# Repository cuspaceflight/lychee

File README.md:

# Lychee

Lychee is a HAB (high-altitude balloon) which serves two main purposes:
- An induction project for new members looking to get hands-on building and launching a HAB.
- A test bed for prototype Martlet IV electronics.

## Motivation
After many years stuck in development hell, Project Strix (Martlet IV's avionics system) was ready for
hardware prototyping and flight testing. But flight testing avionics is difficult, especially on a budget;
so we decided to return to the society's roots and bring back our dormant HAB program.

With rough designs already complete for Martlet IV's eventual launch, we decided to port the flight
computer into a less modular form factor and consolidate modules, to create an extensible dual-board
architecture that allows us to test both fundamental system hardware and prototype future modules through
an expansion slot.

## Aims
The launch aims to test several key features and subsystems of the design ahead of construction of
final Project Strix flight hardware. In summary, these are:
- understand the embedded systems prototyping and development process for the STM32 + ChibiOS/RT stack
- perform real-time altimetry through a combination of
  - 2x redudant barometers
  - 1x 6-DoF IMU
  - 1x GPS
- relay telemetry through our custom ISM-band radio system
- verify the electrical performance of our 'blackbox' flight data recorder

## Using This Repository
This repository contains the electrical and software design files for the project. PCB designs were created
in KiCad 6, and the software was written for ChibiOS/RT. To install the dependency submodules, run
`git submodule update --init` from the root directory.

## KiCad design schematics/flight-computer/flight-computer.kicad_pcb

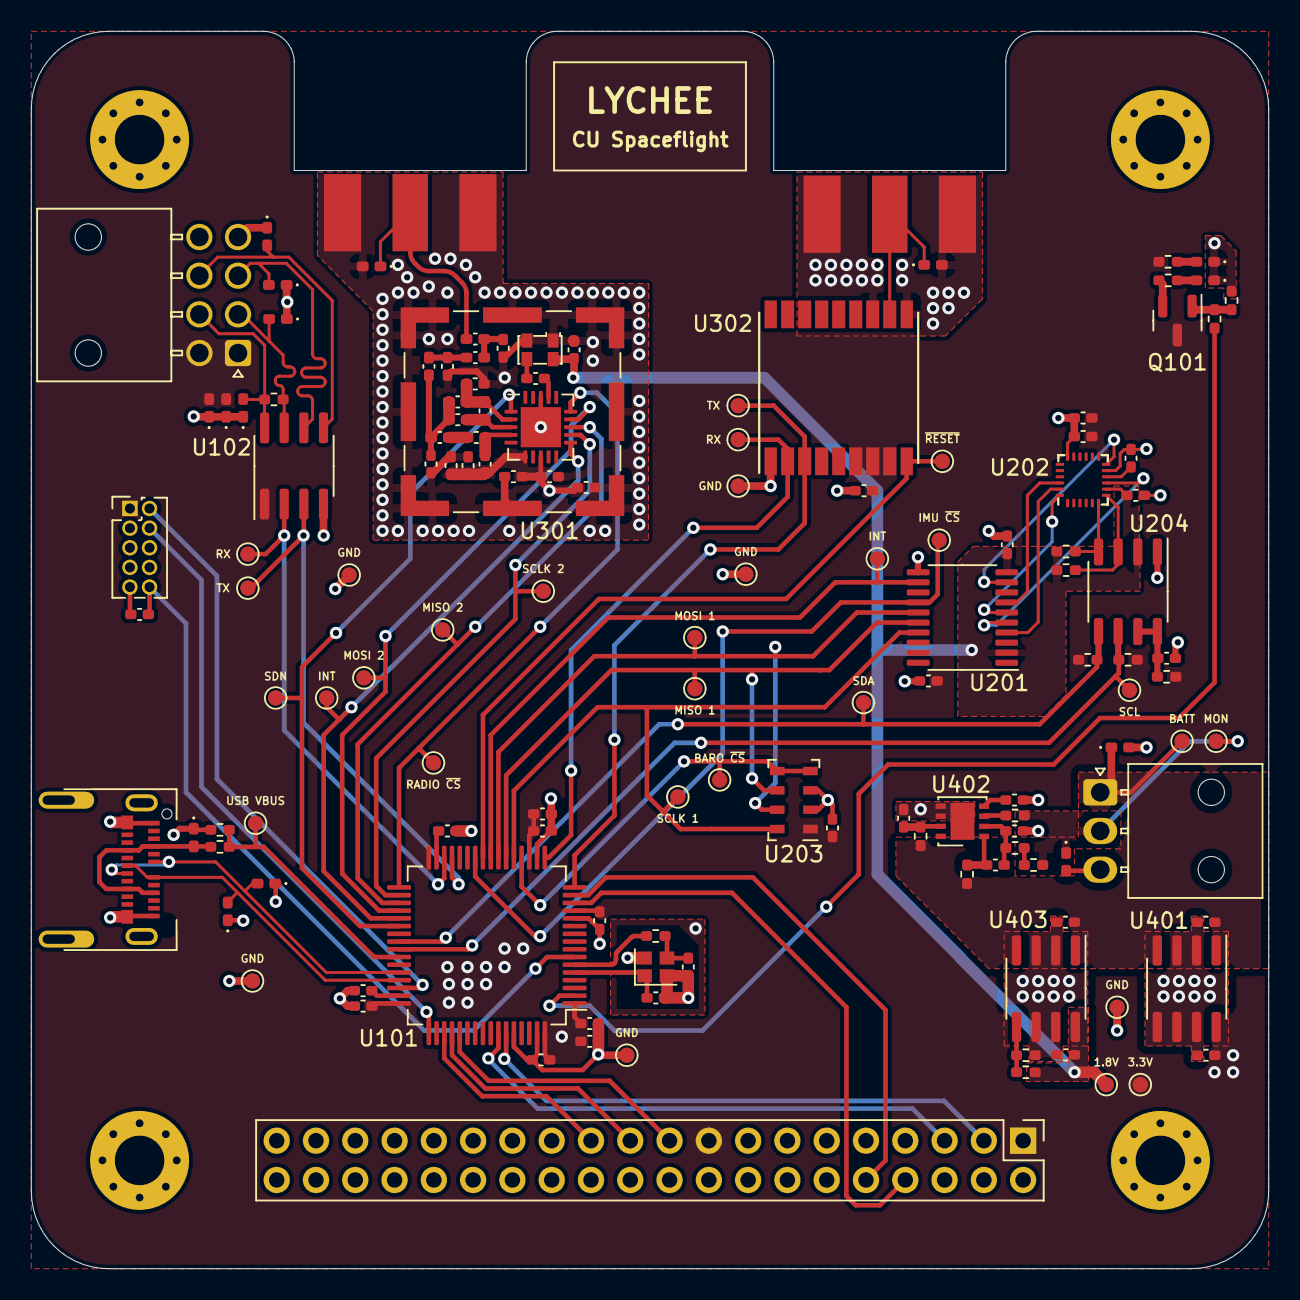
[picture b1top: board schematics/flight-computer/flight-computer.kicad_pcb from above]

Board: 4 copper layers, 80.0 x 80.0 mm, 139 parts (0 on the bottom side), 79 nets.

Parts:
1.8V, 3.3V: TestPoint
BARO ~{CS}: TestPoint
BATT: TestPoint
C101: 1µ; C_0402
C102, C103, C105, C106, C107, C110, C201, C202, C203, C205, C207, C208, C301, C311, C314, C403, C404, C405: 100n; C_0402
C104: 4µ7; C_0402
C108, C109: 2µ2; C_0402
C111, C112: 10p; C_0402
C204, C310: 2u2; C_0402
C206: 10n; C_0402
C302: 2n; C_0402
C303: 5p1; C_0402
C304: 6n8; C_0402
C305, C306: 3p3; C_0402
C307: 1p2; C_0402
C308: 3p; C_0402
C309: 1u; C_0402
C312: 220p; C_0402
C313: 100p; C_0402
C401, C402, C407, C408: 10u; C_0402
C406: 330n; C_0402
D101, D102, D103, D104, D107, D108, D109, D110, D111, D112, D113, D114, D115: D_ESD; D_0402
D105: RED; LED_0402
D106: YLW; LED_0402
GND: TestPoint
GND#2, GND#3, GND#4, GND#5, GND#6: TestPoint
H101, H102, H103, H104: MountingHole_Pad
IMU ~{CS}: TestPoint
INT: TestPoint
INT#2: TestPoint
J101: BATT; Molex_Nano-Fit_105313-1103
J102: GPS; SMA-Edge
J103: TELEM; SMA-Edge
J104: Expansion Slot; Header_RaspberryPi
J105: USB C; USB_C
J106: SWD; Header_SWD
J107: BLACKBOX; Molex_Nano-Fit_105314-1108
J301: BMI-S-201
L301: 120n; L_0402
L302: 3n3; L_0402
L303, L305: 12n; L_0402
L304, L307: 24n; L_0402
L306: 18n; L_0402
MISO 1, MISO 2: TestPoint
MON: TestPoint
MOSI 1, MOSI 2: TestPoint
Q101: BSS138
R101, R105, R401, R403, R405: 100; R_0402
R102, R103: 50; R_0402
R104: 110k; R_0402
R106, R107: 10k; R_0402
R108: 120; R_0402
R201, R407: 200k; R_0402
R202, R203, R204, R205: 4k7; R_0402
R402, R404: 160; R_0402
R406: 100k; R_0402
RADIO ~{CS}: TestPoint
RX: TestPoint
RX#2: TestPoint
SCL: TestPoint
SCLK 1, SCLK 2: TestPoint
SDA: TestPoint
SDN: TestPoint
TX: TestPoint
TX#2: TestPoint
U101: STM32F405RGT6
U102: MAX14787E
U201: NXB0108PW-Q100J
U202: ICM-20789
U203: MS5611-01BA
U204: PCA9306
U301: Si4463
U302: MAX-M8
U401, U403: MAX604
U402: BQ29200
USB VBUS: TestPoint
Y101: 26M; Xtal_SMD_2016
Y301: LFTCXO068373

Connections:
1v8: 1.8V.1, C203.2, C206.2, C301.1, C408.1, R204.2, R205.2, R406.2, U201.2 (VCC(A)), U201.10 (OE), U202.8 (VDDIO), U204.2 (VREF1), U403.8 (OUT), Y301.4 (VCC)
3v3: 3.3V.1, C101.2, C102.2, C103.2, C104.2, C105.2, C106.2, C107.2, C202.2, C204.2, C205.2, C207.2, C309.1, C310.1, C311.1, C312.1, C313.1, C314.2, C402.1, D112.2, D113.2, J104.1, J104.17, J106.1, J107.1, J107.2, L301.1, Q101.3 (D), R102.2, R201.2, R202.2, R203.2, U101.1 (VBAT), U101.13 (VDDA), U101.19 (VDD), U101.32 (VDD), U101.48 (VDD), U101.64 (VDD), U102.1 (VDD), U201.19 (VCC(B)), U202.13 (VDD), U203.1 (VDD), U301.6 (VDD), U301.8 (VDD), U302.6 (V_BCKP), U302.7 (VCC_IO), U302.8 (VCC), U401.8 (OUT)
/Altimeter/SCL_1v8: R205.1, U202.7 (PR_CL), U204.3 (SCL1)
/Altimeter/SDA_1v8: R204.1, U202.6 (PR_DA), U204.4 (SDA1)
/BARO_~CS: BARO ~{CS}.1, U101.20 (PA4), U203.4 (CSB), U203.5 (CSB)
/BATT_MON: D102.1, J101.2, MON.1, R403.1, R405.1
/BB_RX+: D114.2, J107.4, R108.1, U102.8 (A)
/BB_RX-: D111.2, J107.3, R108.2, U102.7 (B)
/BB_TX+: D115.2, J107.6, U102.5 (Y)
/BB_TX-: D110.2, J107.5, U102.6 (Z)
/GPS_~RESET: U101.25 (PC5), U302.9 (~RESET)
/I2C1_SCL: J104.5, U101.58 (PB6)
/I2C1_SDA: J104.3, U101.59 (PB7)
/I2C3_SCL: R202.1, SCL.1, U101.41 (PA8), U204.6 (SCL2)
/I2C3_SDA: R203.1, SDA.1, U101.40 (PC9), U204.5 (SDA2)
/IMU_INT: INT#2.1, U101.24 (PC4), U201.12 (B8)
/IMU_~CS: IMU ~{CS}.1, U101.26 (PB0), U201.14 (B6)
/LED: R101.1, U101.2 (PC13)
/NRST: C110.2, J106.10, U101.7 (NRST)
/RADIO_SDN: SDN.1, U101.38 (PC7), U301.1 (SDN)
/RADIO_~CS: RADIO ~{CS}.1, U101.33 (PB12), U301.15 (nSEL)
/RADIO_~INT: INT.1, U101.37 (PC6), U301.11 (nIRQ)
/Radio/ANT_GPS: D103.1, J102.1 (RF), U302.11 (RF_IN)
/Radio/ANT_TLM: D104.1, J103.1 (RF), L305.2
/Radio/RX+: C308.1, L306.2, L307.1, U301.2 (RXp)
/Radio/RX-: C307.1, L306.1, U301.3 (RXn)
/Radio/TX: C303.1, L301.2, U301.4 (TX)
/SPI1_MISO: MISO 1.1, U101.22 (PA6), U201.16 (B4), U203.6 (SDO)
/SPI1_MOSI: MOSI 1.1, U101.23 (PA7), U201.15 (B5), U203.7 (SDI/SDA)
/SPI1_SCLK: SCLK 1.1, U101.21 (PA5), U201.17 (B3), U203.8 (SCLK)
/SPI2_MISO: MISO 2.1, U101.35 (PB14), U301.13 (SDO)
/SPI2_MOSI: MOSI 2.1, U101.36 (PB15), U301.14 (SDI)
/SPI2_SCLK: SCLK 2.1, U101.34 (PB13), U301.12 (SCLK)
/SPI3_MISO: J104.21, U101.52 (PC11)
/SPI3_MOSI: J104.19, U101.53 (PC12)
/SPI3_SCLK: J104.23, U101.51 (PC10)
/SWDCLK: J106.4, U101.49 (PA14)
/SWDIO: J106.2, U101.46 (PA13)
/UART4_RX: J104.10, U101.15 (PA1)
/UART4_TX: J104.8, U101.14 (PA0)
/USART2_RX: RX#2.1, U101.17 (PA3), U302.2 (TXD)
/USART2_TX: TX.1, U101.16 (PA2), U302.3 (RXD)
/USART3_RX: RX.1, U101.30 (PB11), U102.2 (RO)
/USART3_TX: TX#2.1, U101.29 (PB10), U102.3 (DI)
/USB_FS_D+: D109.2, J105.A6 (D+), J105.B6 (D+), U101.44 (PA11)
/USB_FS_D-: D108.2, J105.A7 (D-), J105.B7 (D-), U101.45 (PA12)
/USB_FS_VBUS: R106.1, R107.2, U101.42 (PA9), USB VBUS.1
GND: C101.1, C102.1, C103.1, C104.1, C105.1, C106.1, C107.1, C108.1, C109.1, C110.1, C111.1, C112.1, C201.1, C202.1, C203.1, C204.1, C205.1, C206.1, C207.1, C208.1, C301.2, C304.2, C305.2, C306.2, C308.2, C309.2, C310.2, C311.2, C312.2, C313.2, C314.1, C401.2, C402.2, C404.2, C405.2, C406.2, C407.2, C408.2, D101.2, D102.2, D103.2, D104.2, D105.1, D106.1, D107.1, D108.1, D109.1, D110.1, D111.1, D112.1, D113.1, D114.1, D115.1, GND.1, GND#2.1, GND#3.1, GND#4.1, GND#5.1, GND#6.1, H101.1, H102.1, H103.1, H104.1, J101.3, J102.2 (GND), J103.2 (GND), J104.6, J104.9, J104.14, J104.20, J104.25, J104.30, J104.34, J104.39, J105.A1 (GND), J105.A12 (GND), J105.B1 (GND), J105.B12 (GND), J105.S1 (SHIELD), J106.3, J106.5, J106.9, J107.7, J107.8, J301.1 (Shield), R104.1, R107.1, R407.2, U101.12 (VSSA), U101.18 (VSS), U101.60 (BOOT0), U101.63 (VSS), U102.4 (GND), U201.11 (GND), U202.11 (FSYNC), U202.18 (GND), U203.2 (PS), U203.3 (GND), U204.1 (GND), U301.18 (GND), U301.21 (GND), U302.1 (GND), U302.10 (GND), U302.12 (GND), U401.2 (GND), U401.3 (GND), U401.5 (SET), U401.6 (GND), U401.7 (GND), U402.5 (GND), U402.6 (~CB_EN), U402.9 (PGND), U403.2 (GND), U403.3 (GND), U403.6 (GND), U403.7 (GND), Y101.2, Y101.4, Y301.1 (GND), Y301.2 (GND)
unnamed: C108.2, U101.31 (VCAP_1)
unnamed: C109.2, U101.47 (VCAP_2)
unnamed: C111.2, U101.5 (PH0), Y101.1
unnamed: C112.2, R105.1, Y101.3
unnamed: C201.2, U202.10 (REGOUT)
unnamed: C208.2, R201.1, U204.7 (VREF2), U204.8 (EN)
unnamed: C302.1, Y301.3 (OUT)
unnamed: C302.2, U301.17 (XIN)
unnamed: C303.2, L302.1
unnamed: C304.1, C307.2, L302.2, L303.1, L307.2
unnamed: C305.1, L303.2, L304.1
unnamed: C306.1, L304.2, L305.1
unnamed: C403.1, R402.2, U402.1 (VC2)
unnamed: C403.2, C405.1, R404.2, U402.2 (VC1)
unnamed: C404.1, R401.2, U402.7 (VDD)
unnamed: C406.1, U402.4 (CD)
unnamed: D105.2, R102.1
unnamed: D106.2, R103.1
unnamed: D107.2, J105.A4 (VBUS), J105.A9 (VBUS), J105.B4 (VBUS), J105.B9 (VBUS), R106.2
unnamed: Q101.1 (G), R101.2, R104.2
unnamed: Q101.2 (S), R103.2
unnamed: R105.2, U101.6 (PH1)
unnamed: R403.2, R404.1
unnamed: R405.2, U402.3 (VC1_CB)
unnamed: R406.1, R407.1, U403.5 (SET)
unnamed: U201.4 (A3), U202.23 (SCL/SCLK)
unnamed: U201.5 (A4), U202.9 (SDO/AD0)
unnamed: U201.6 (A5), U202.24 (SDA/SDI)
unnamed: U201.7 (A6), U202.22 (~CS)
unnamed: U201.9 (A8), U202.12 (INT)
VBATT: BATT.1, C401.1, C407.1, D101.1, J101.1, R401.1, R402.1, U401.1 (IN), U401.4 (~OFF), U403.1 (IN), U403.4 (~OFF)

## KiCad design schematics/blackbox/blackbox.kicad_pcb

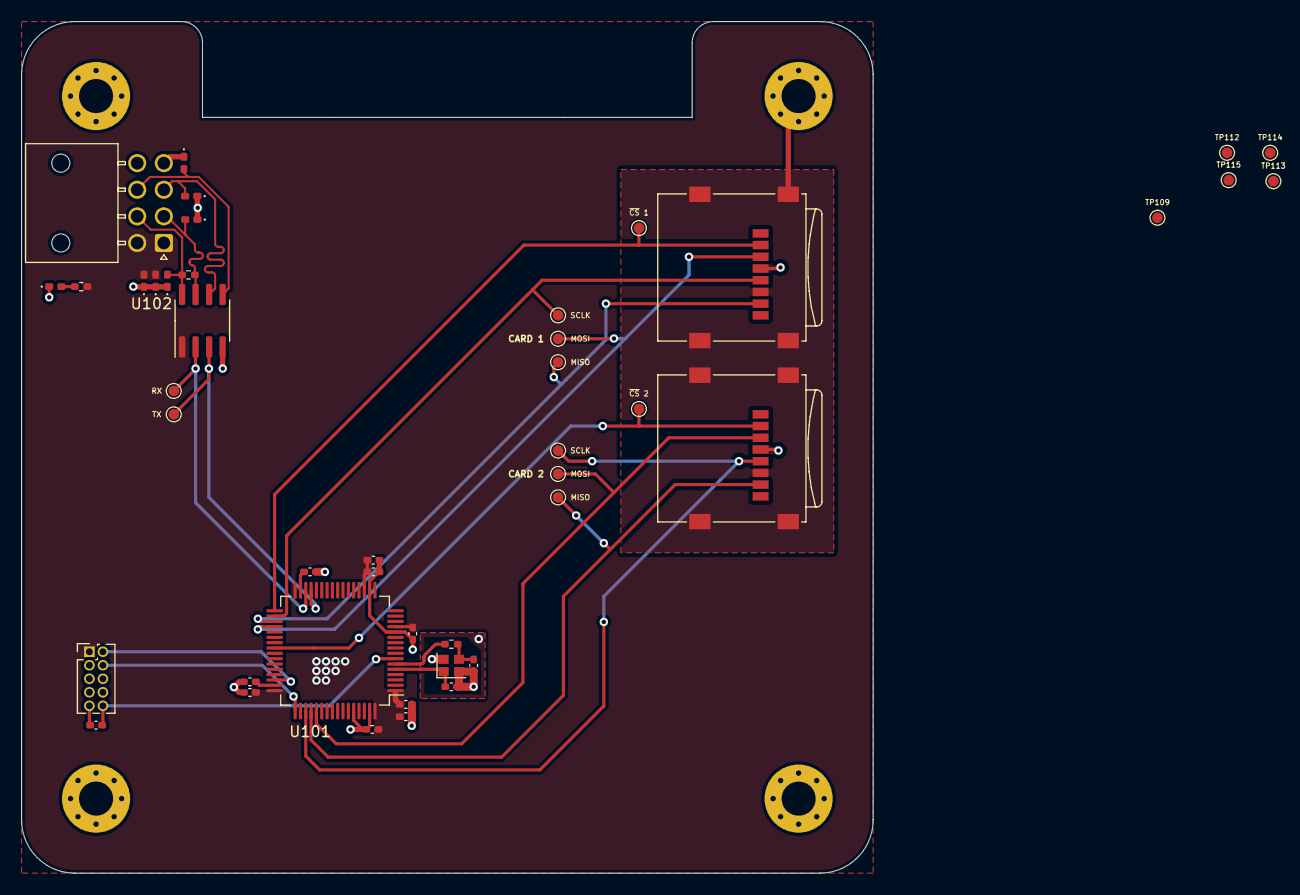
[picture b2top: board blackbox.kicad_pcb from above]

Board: 4 copper layers, 80.0 x 80.0 mm, 46 parts (0 on the bottom side), 25 nets.

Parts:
C101: 1µ; C_0402
C102, C103, C105, C106, C107, C110: 100n; C_0402
C104: 4µ7; C_0402
C108, C109: 2µ2; C_0402
C111, C112: 10p; C_0402
D101: RED; LED_0402
D102, D103, D104, D105, D106, D107: D_ESD; D_0402
H101, H102, H103, H104: MountingHole_Pad
J101, J102: Micro_SD_Card; microSD_HC_Wuerth_693072010801
J103: SWD; Header_SWD
J104: F_COMPUTER; Molex_Nano-Fit_105314-1108
MISO: TestPoint
MISO#2: TestPoint
MOSI: TestPoint
MOSI#2: TestPoint
R101: 50; R_0402
R102: 100; R_0402
R103: 120; R_0402
RX: TestPoint
SCLK: TestPoint
SCLK#2: TestPoint
TP109, TP112, TP113, TP114, TP115: TestPoint
TX: TestPoint
U101: STM32F405RGT6
U102: MAX14787E
Y101: 26M; Xtal_SMD_2016

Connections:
3v3: C101.2, C102.2, C103.2, C104.2, C105.2, C106.2, C107.2, D104.2, D105.2, J101.4 (VDD), J102.4 (VDD), J103.1, J104.1, J104.2, R101.2, TP109.1, U101.1 (VBAT), U101.13 (VDDA), U101.19 (VDD), U101.32 (VDD), U101.48 (VDD), U101.64 (VDD), U102.1 (VDD)
/BB_RX+: D106.2, J104.4, R103.1, U102.8 (A)
/BB_RX-: D103.2, J104.3, R103.2, U102.7 (B)
/BB_TX+: D107.2, J104.6, U102.5 (Y)
/BB_TX-: D102.2, J104.5, U102.6 (Z)
/NRST: C110.2, J103.10, U101.7 (NRST)
/SD1_~CS: J101.2 (DAT3/CD), U101.33 (PB12)
/SD2_~CS: J102.2 (DAT3/CD), U101.40 (PC9)
/SPI2_MISO: J101.7 (DAT0), MISO#2.1, U101.35 (PB14)
/SPI2_MOSI: J101.3 (CMD), MOSI.1, U101.36 (PB15)
/SPI2_SCLK: J101.5 (CLK), SCLK.1, U101.34 (PB13)
/SPI3_MISO: J102.7 (DAT0), MISO.1, U101.52 (PC11)
/SPI3_MOSI: J102.3 (CMD), MOSI#2.1, U101.53 (PC12)
/SPI3_SCLK: J102.5 (CLK), SCLK#2.1, U101.51 (PC10)
/SWDCLK: J103.4, U101.49 (PA14)
/SWDIO: J103.2, U101.46 (PA13)
/USART3_RX: RX.1, U101.30 (PB11), U102.2 (RO)
/USART3_TX: TX.1, U101.29 (PB10), U102.3 (DI)
GND: C101.1, C102.1, C103.1, C104.1, C105.1, C106.1, C107.1, C108.1, C109.1, C110.1, C111.1, C112.1, D101.1, D102.1, D103.1, D104.1, D105.1, D106.1, D107.1, H101.1, H102.1, H103.1, H104.1, J101.6 (VSS), J101.9 (SHIELD), J102.6 (VSS), J102.9 (SHIELD), J103.3, J103.5, J103.9, J104.7, J104.8, TP112.1, TP113.1, TP114.1, TP115.1, U101.12 (VSSA), U101.18 (VSS), U101.60 (BOOT0), U101.63 (VSS), U102.4 (GND), Y101.2, Y101.4
unnamed: C108.2, U101.31 (VCAP_1)
unnamed: C109.2, U101.47 (VCAP_2)
unnamed: C111.2, U101.5 (PH0), Y101.1
unnamed: C112.2, R102.1, Y101.3
unnamed: D101.2, R101.1
unnamed: R102.2, U101.6 (PH1)

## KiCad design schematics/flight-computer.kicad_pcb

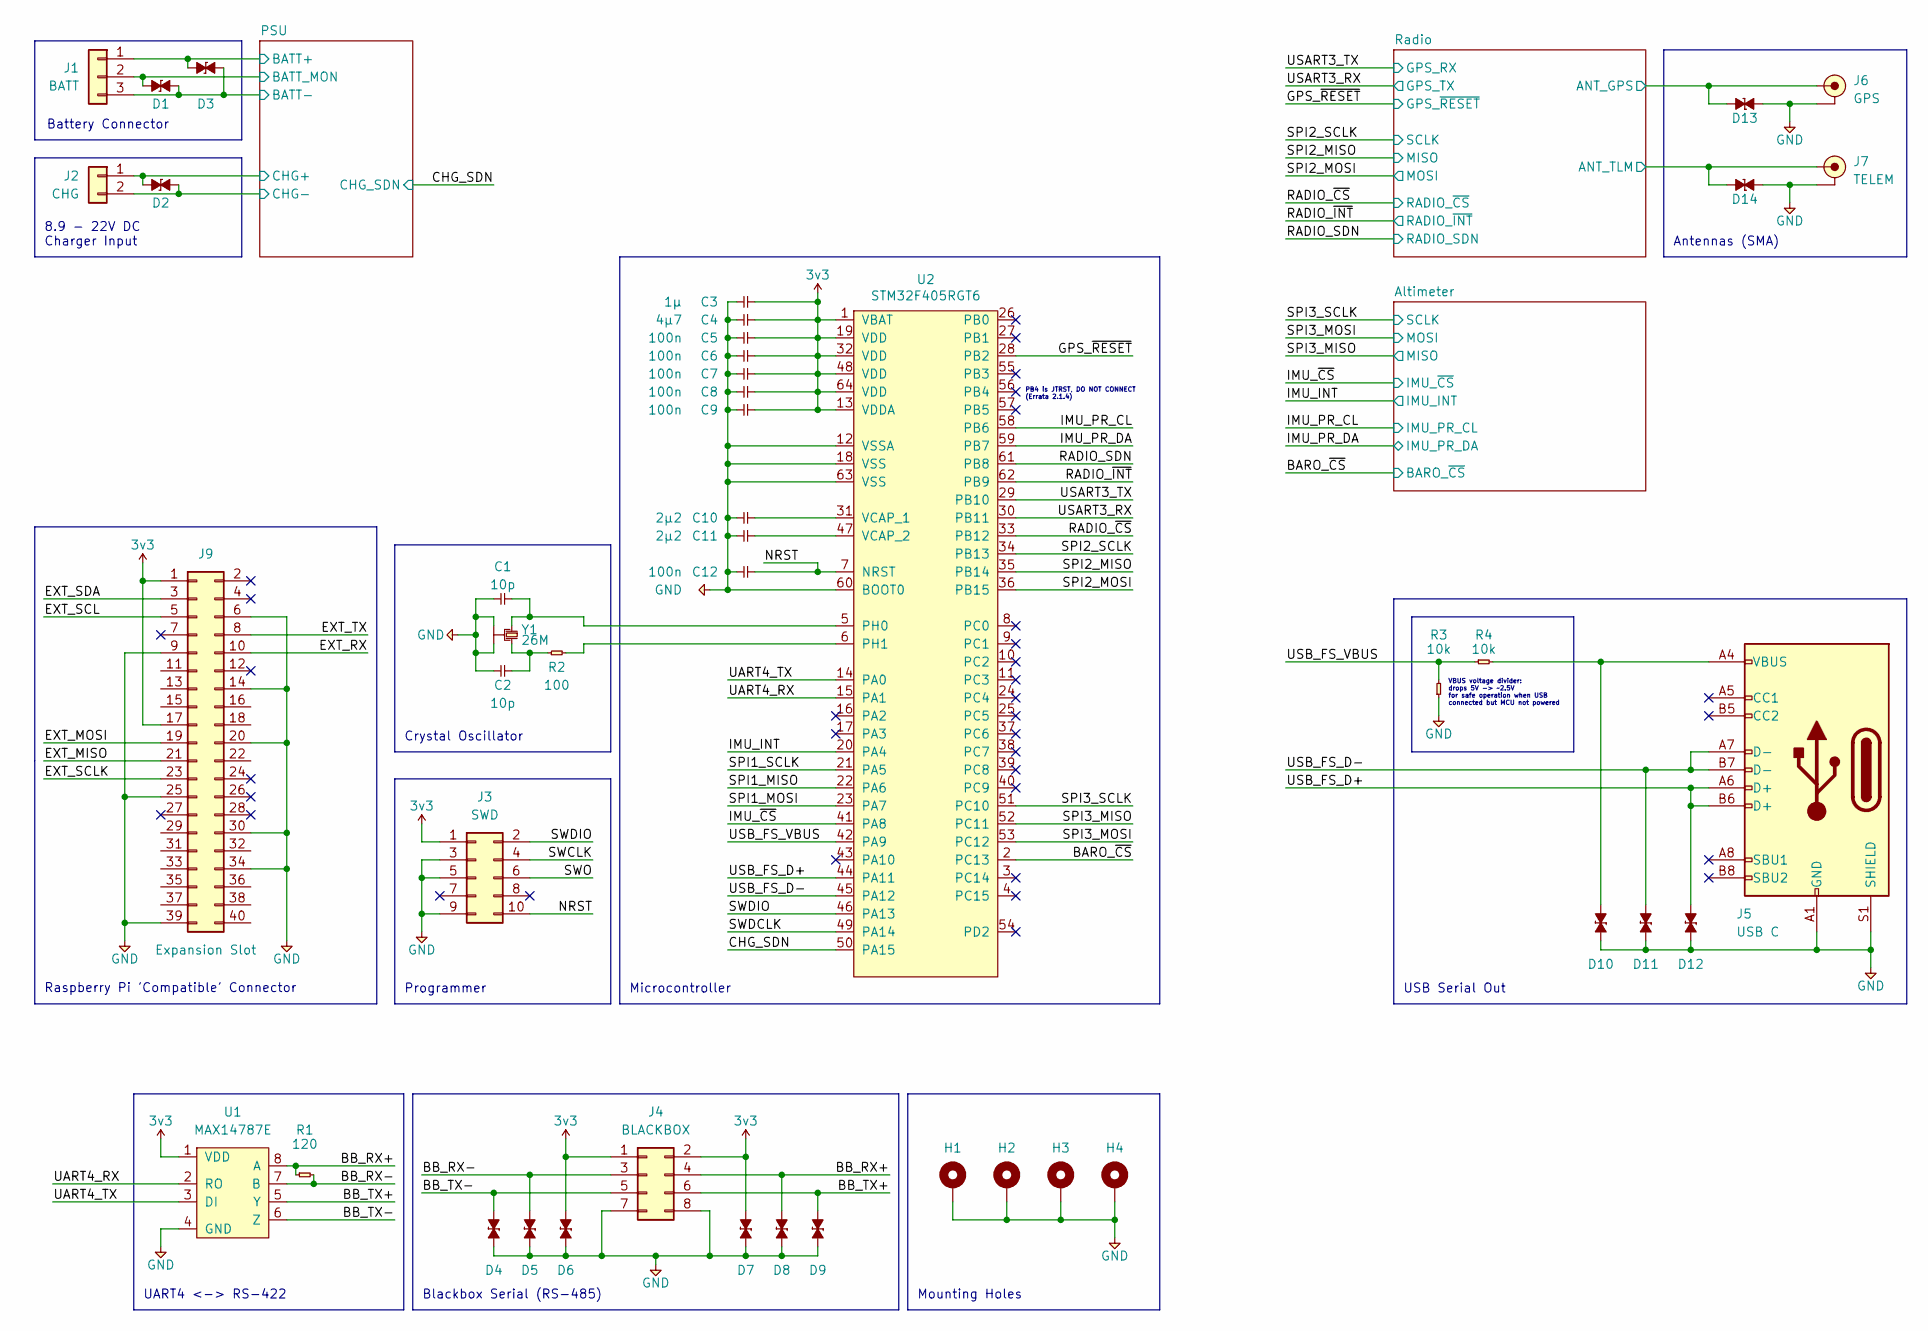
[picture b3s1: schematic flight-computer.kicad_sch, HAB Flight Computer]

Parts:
C1, C2: 10p; C_0402
C3: 1µ; C_0402; Farnell 2496814
C4: 4µ7; C_0402; Farnell 2426952
C5, C6, C7, C8, C9, C12: 100n; C_0402; Farnell 2496771
C10, C11: 2µ2; C_0402; Farnell 2362088
D1, D2, D3, D4, D5, D6, D7, D8, D9, D10, D11, D12, D13, D14: D_ESD; D_0402; Farnell 2368169
H1, H2, H3, H4: MountingHole_Pad
J1: BATT; Molex_Nano-Fit_105313-1103; Farnell 2820685
J2: CHG; Molex_Nano-Fit_105313-1102
J3: SWD; Header_SWD
J4: BLACKBOX; Molex_Nano-Fit_105314-1108
J5: USB C; USB_C; Farnell 2990003
J6: GPS; SMA-Edge; Farnell 1608592
J7: TELEM; SMA-Edge; Farnell 1608592
J9: Expansion Slot; Header_RaspberryPi
R1: 120; R_0402
R2: 100; R_0402
R3, R4: 10k; R_0402
U1: MAX14787E; Farnell 2528531
U2: STM32F405RGT6; Farnell 2064363
Y1: 26M; Xtal-20x16; Farnell 2506952

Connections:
3v3: C3.2, C4.2, C5.2, C6.2, C7.2, C8.2, C9.2, D6.2, D7.2, J3.1, J4.1, J4.2, J9.1, J9.17, U1.1 (VDD), U2.1 (VBAT), U2.13 (VDDA), U2.19 (VDD), U2.32 (VDD), U2.48 (VDD), U2.64 (VDD); also elsewhere on the board
/BARO_~CS: U2.2 (PC13); also elsewhere on the board
/BB_RX+: D8.2, J4.4, R1.1, U1.8 (A)
/BB_RX-: D5.2, J4.3, R1.2, U1.7 (B)
/BB_TX+: D9.2, J4.6, U1.5 (Y)
/BB_TX-: D4.2, J4.5, U1.6 (Z)
/CHG_SDN: U2.50 (PA15); also elsewhere on the board
/EXT_MISO: J9.21
/EXT_MOSI: J9.19
/EXT_RX: J9.10
/EXT_SCL: J9.5
/EXT_SCLK: J9.23
/EXT_SDA: J9.3
/EXT_TX: J9.8
/GPS_~RESET: U2.28 (PB2); also elsewhere on the board
/IMU_INT: U2.20 (PA4); also elsewhere on the board
/IMU_PR_CL: U2.58 (PB6); also elsewhere on the board
/IMU_PR_DA: U2.59 (PB7); also elsewhere on the board
/IMU_~CS: U2.41 (PA8); also elsewhere on the board
/NRST: C12.2, J3.10, U2.7 (NRST)
/PSU/BATT_MON: D1.1, J1.2; also elsewhere on the board
/PSU/CHG+: D2.1, J2.1; also elsewhere on the board
/RADIO_SDN: U2.61 (PB8); also elsewhere on the board
/RADIO_~CS: U2.33 (PB12); also elsewhere on the board
/RADIO_~INT: U2.62 (PB9); also elsewhere on the board
/Radio/ANT_GPS: D13.1, J6.1 (RF); also elsewhere on the board
/Radio/ANT_TLM: D14.1, J7.1 (RF); also elsewhere on the board
/SPI1_MISO: U2.22 (PA6)
/SPI1_MOSI: U2.23 (PA7)
/SPI1_SCLK: U2.21 (PA5)
/SPI2_MISO: U2.35 (PB14); also elsewhere on the board
/SPI2_MOSI: U2.36 (PB15); also elsewhere on the board
/SPI2_SCLK: U2.34 (PB13); also elsewhere on the board
/SPI3_MISO: U2.52 (PC11); also elsewhere on the board
/SPI3_MOSI: U2.53 (PC12); also elsewhere on the board
/SPI3_SCLK: U2.51 (PC10); also elsewhere on the board
/SWCLK: J3.4
/SWDCLK: U2.49 (PA14)
/SWDIO: J3.2, U2.46 (PA13)
/SWO: J3.6
/UART4_RX: U1.2 (RO), U2.15 (PA1)
/UART4_TX: U1.3 (DI), U2.14 (PA0)
/USART3_RX: U2.30 (PB11); also elsewhere on the board
/USART3_TX: U2.29 (PB10); also elsewhere on the board
/USB_FS_D+: D12.2, J5.A6 (D+), J5.B6 (D+), U2.44 (PA11)
/USB_FS_D-: D11.2, J5.A7 (D-), J5.B7 (D-), U2.45 (PA12)
/USB_FS_VBUS: R3.2, R4.1, U2.42 (PA9)
GND: C1.1, C2.1, C3.1, C4.1, C5.1, C6.1, C7.1, C8.1, C9.1, C10.1, C11.1, C12.1, D1.2, D2.2, D3.2, D4.1, D5.1, D6.1, D7.1, D8.1, D9.1, D10.1, D11.1, D12.1, D13.2, D14.2, H1.1, H2.1, H3.1, H4.1, J1.3, J2.2, J3.3, J3.5, J3.9, J4.7, J4.8, J5.A1 (GND), J5.A12 (GND), J5.B1 (GND), J5.B12 (GND), J5.S1 (SHIELD), J6.2 (GND), J7.2 (GND), J9.6, J9.9, J9.14, J9.20, J9.25, J9.30, J9.34, J9.39, R3.1, U1.4 (GND), U2.12 (VSSA), U2.18 (VSS), U2.60 (BOOT0), U2.63 (VSS), Y1.2, Y1.4; also elsewhere on the board
unnamed: C1.2, U2.5 (PH0), Y1.1
unnamed: C2.2, R2.1, Y1.3
unnamed: C10.2, U2.31 (VCAP_1)
unnamed: C11.2, U2.47 (VCAP_2)
unnamed: D10.2, J5.A4 (VBUS), J5.A9 (VBUS), J5.B4 (VBUS), J5.B9 (VBUS), R4.2
unnamed: R2.2, U2.6 (PH1)
VBATT: D3.1, J1.1; also elsewhere on the board

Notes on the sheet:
Blackbox Serial (RS-485)
USB Serial Out
PB4 is JTRST, DO NOT CONNECT (Errata 2.1.4)
Battery Connector
Mounting Holes
Crystal Oscillator
UART4 <-> RS-422
Programmer
VBUS voltage divider: drops 5V -> ~2.5V for safe operation when USB connected but MCU not powered
Microcontroller
Raspberry Pi 'Compatible' Connector
8.9 - 22V DC Charger Input
Antennas (SMA)

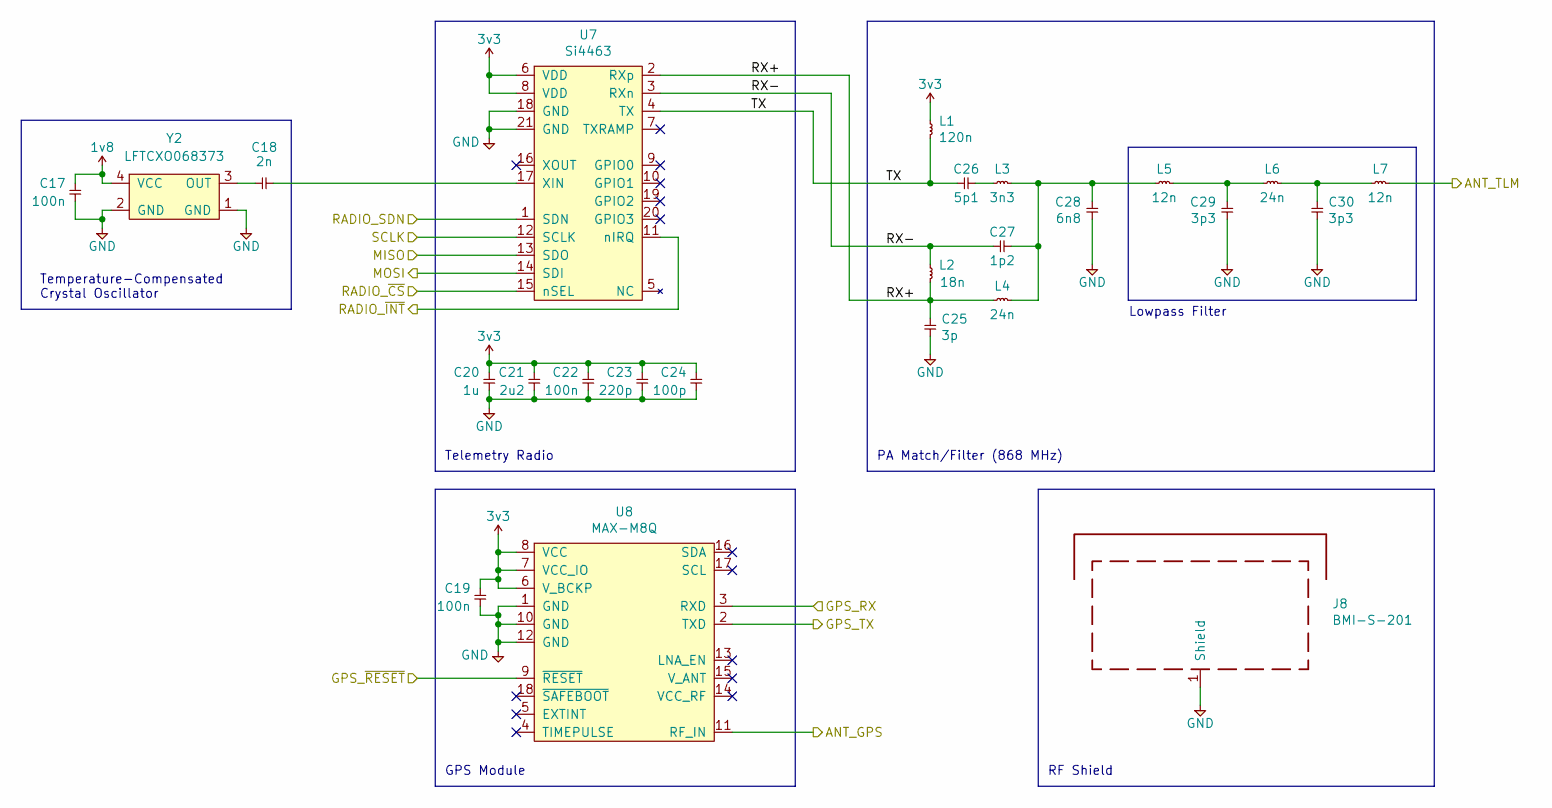
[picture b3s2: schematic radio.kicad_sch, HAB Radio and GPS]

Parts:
C17, C19, C22: 100n; C_0402
C18: 2n; C_0402
C20: 1u; C_0402
C21: 2u2; C_0402
C23: 220p; C_0402
C24: 100p; C_0402
C25: 3p; C_0402
C26: 5p1; C_0402
C27: 1p2; C_0402
C28: 6n8; C_0402
C29, C30: 3p3; C_0402
J8: BMI-S-201
L1: 120n; L_0402
L2: 18n; L_0402
L3: 3n3; L_0402
L4, L6: 24n; L_0402
L5, L7: 12n; L_0402
U7: Si4463; Farnell 2462637
U8: MAX-M8Q
Y2: LFTCXO068373; Farnell 2627327

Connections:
1v8: C17.1, Y2.4 (VCC); also elsewhere on the board
3v3: C19.2, C20.1, C21.1, C22.1, C23.1, C24.1, L1.1, U7.6 (VDD), U7.8 (VDD), U8.6 (V_BCKP), U8.7 (VCC_IO), U8.8 (VCC); also elsewhere on the board
/GPS_~RESET: U8.9 (~RESET); also elsewhere on the board
/RADIO_SDN: U7.1 (SDN); also elsewhere on the board
/RADIO_~CS: U7.15 (nSEL); also elsewhere on the board
/RADIO_~INT: U7.11 (nIRQ); also elsewhere on the board
/Radio/ANT_GPS: U8.11 (RF_IN); also elsewhere on the board
/Radio/ANT_TLM: L7.2; also elsewhere on the board
/Radio/RX+: C25.1, L2.2, L4.1, U7.2 (RXp)
/Radio/RX-: C27.1, L2.1, U7.3 (RXn)
/Radio/TX: C26.1, L1.2, U7.4 (TX)
/SPI2_MISO: U7.13 (SDO); also elsewhere on the board
/SPI2_MOSI: U7.14 (SDI); also elsewhere on the board
/SPI2_SCLK: U7.12 (SCLK); also elsewhere on the board
/USART3_RX: U8.2 (TXD); also elsewhere on the board
/USART3_TX: U8.3 (RXD); also elsewhere on the board
GND: C17.2, C19.1, C20.2, C21.2, C22.2, C23.2, C24.2, C25.2, C28.2, C29.2, C30.2, J8.1 (Shield), U7.18 (GND), U7.21 (GND), U8.1 (GND), U8.10 (GND), U8.12 (GND), Y2.1 (GND), Y2.2 (GND); also elsewhere on the board
unnamed: C18.1, Y2.3 (OUT)
unnamed: C18.2, U7.17 (XIN)
unnamed: C26.2, L3.1
unnamed: C27.2, C28.1, L3.2, L4.2, L5.1
unnamed: C29.1, L5.2, L6.1
unnamed: C30.1, L6.2, L7.1

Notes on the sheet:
PA Match/Filter (868 MHz)
Lowpass Filter
GPS Module
Telemetry Radio
Temperature-Compensated Crystal Oscillator
RF Shield

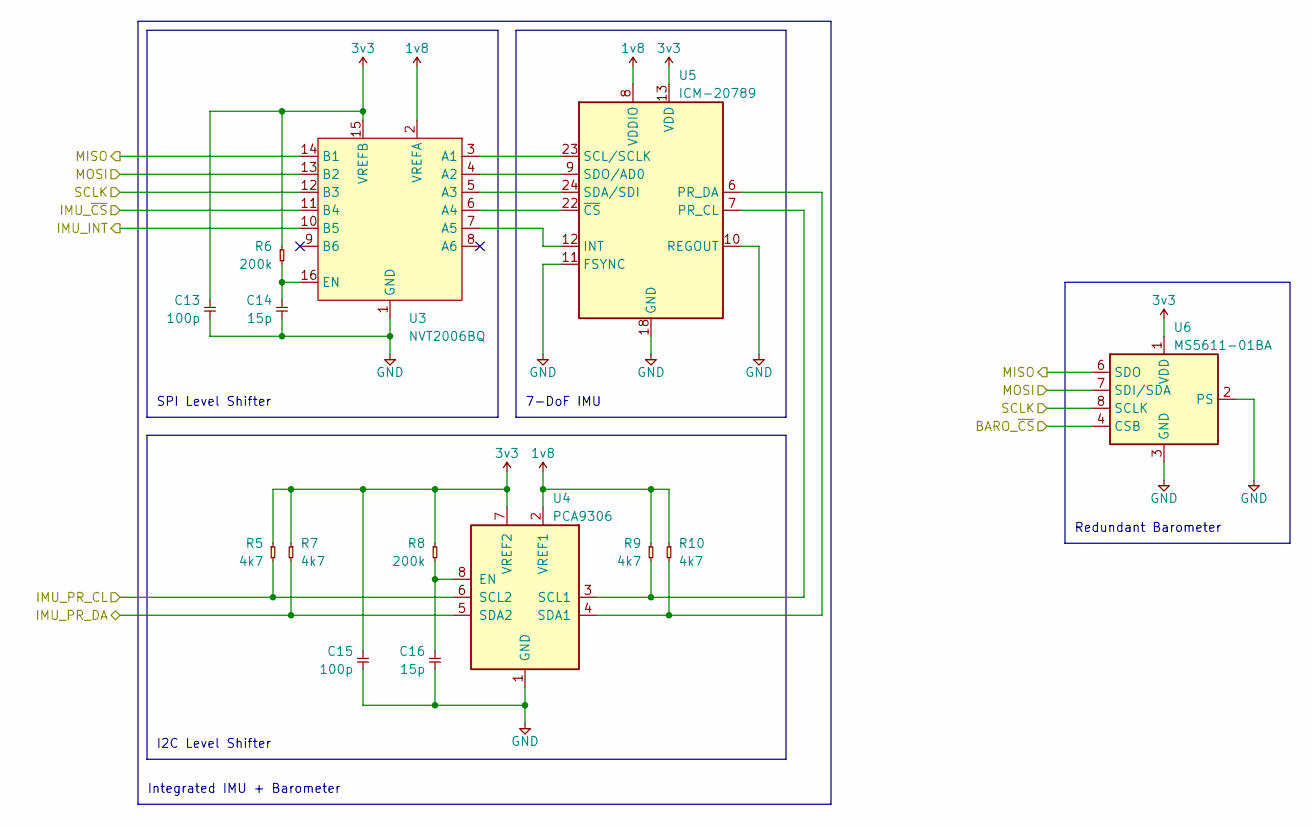
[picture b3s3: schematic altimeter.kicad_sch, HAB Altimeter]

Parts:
C13, C15: 100p; C_0402
C14, C16: 15p; C_0402
R5, R7, R9, R10: 4k7; R_0402
R6, R8: 200k; R_0402
U3: NVT2006BQ
U4: PCA9306
U5: ICM-20789
U6: MS5611-01BA

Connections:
1v8: R9.1, R10.1, U3.2 (VREFA), U4.2 (VREF1), U5.8 (VDDIO); also elsewhere on the board
3v3: C13.2, C15.2, R5.1, R6.1, R7.1, R8.1, U3.15 (VREFB), U4.7 (VREF2), U5.13 (VDD), U6.1 (VDD); also elsewhere on the board
/BARO_~CS: U6.4 (CSB), U6.5 (CSB); also elsewhere on the board
/IMU_INT: U3.10 (B5); also elsewhere on the board
/IMU_PR_CL: R5.2, U4.6 (SCL2); also elsewhere on the board
/IMU_PR_DA: R7.2, U4.5 (SDA2); also elsewhere on the board
/IMU_~CS: U3.11 (B4); also elsewhere on the board
/SPI3_MISO: U3.14 (B1), U6.6 (SDO); also elsewhere on the board
/SPI3_MOSI: U3.13 (B2), U6.7 (SDI/SDA); also elsewhere on the board
/SPI3_SCLK: U3.12 (B3), U6.8 (SCLK); also elsewhere on the board
GND: C13.1, C14.1, C15.1, C16.1, U3.1 (GND), U4.1 (GND), U5.10 (REGOUT), U5.11 (FSYNC), U5.18 (GND), U5.20 (NC), U6.2 (PS), U6.3 (GND); also elsewhere on the board
unnamed: C14.2, R6.2, U3.16 (EN)
unnamed: C16.2, R8.2, U4.8 (EN)
unnamed: R9.2, U4.3 (SCL1), U5.7 (PR_CL)
unnamed: R10.2, U4.4 (SDA1), U5.6 (PR_DA)
unnamed: U3.3 (A1), U5.23 (SCL/SCLK)
unnamed: U3.4 (A2), U5.9 (SDO/AD0)
unnamed: U3.5 (A3), U5.24 (SDA/SDI)
unnamed: U3.6 (A4), U5.22 (~CS)
unnamed: U3.7 (A5), U5.12 (INT)

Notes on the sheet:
SPI Level Shifter
Integrated IMU + Barometer
Redundant Barometer
I2C Level Shifter
7-DoF IMU

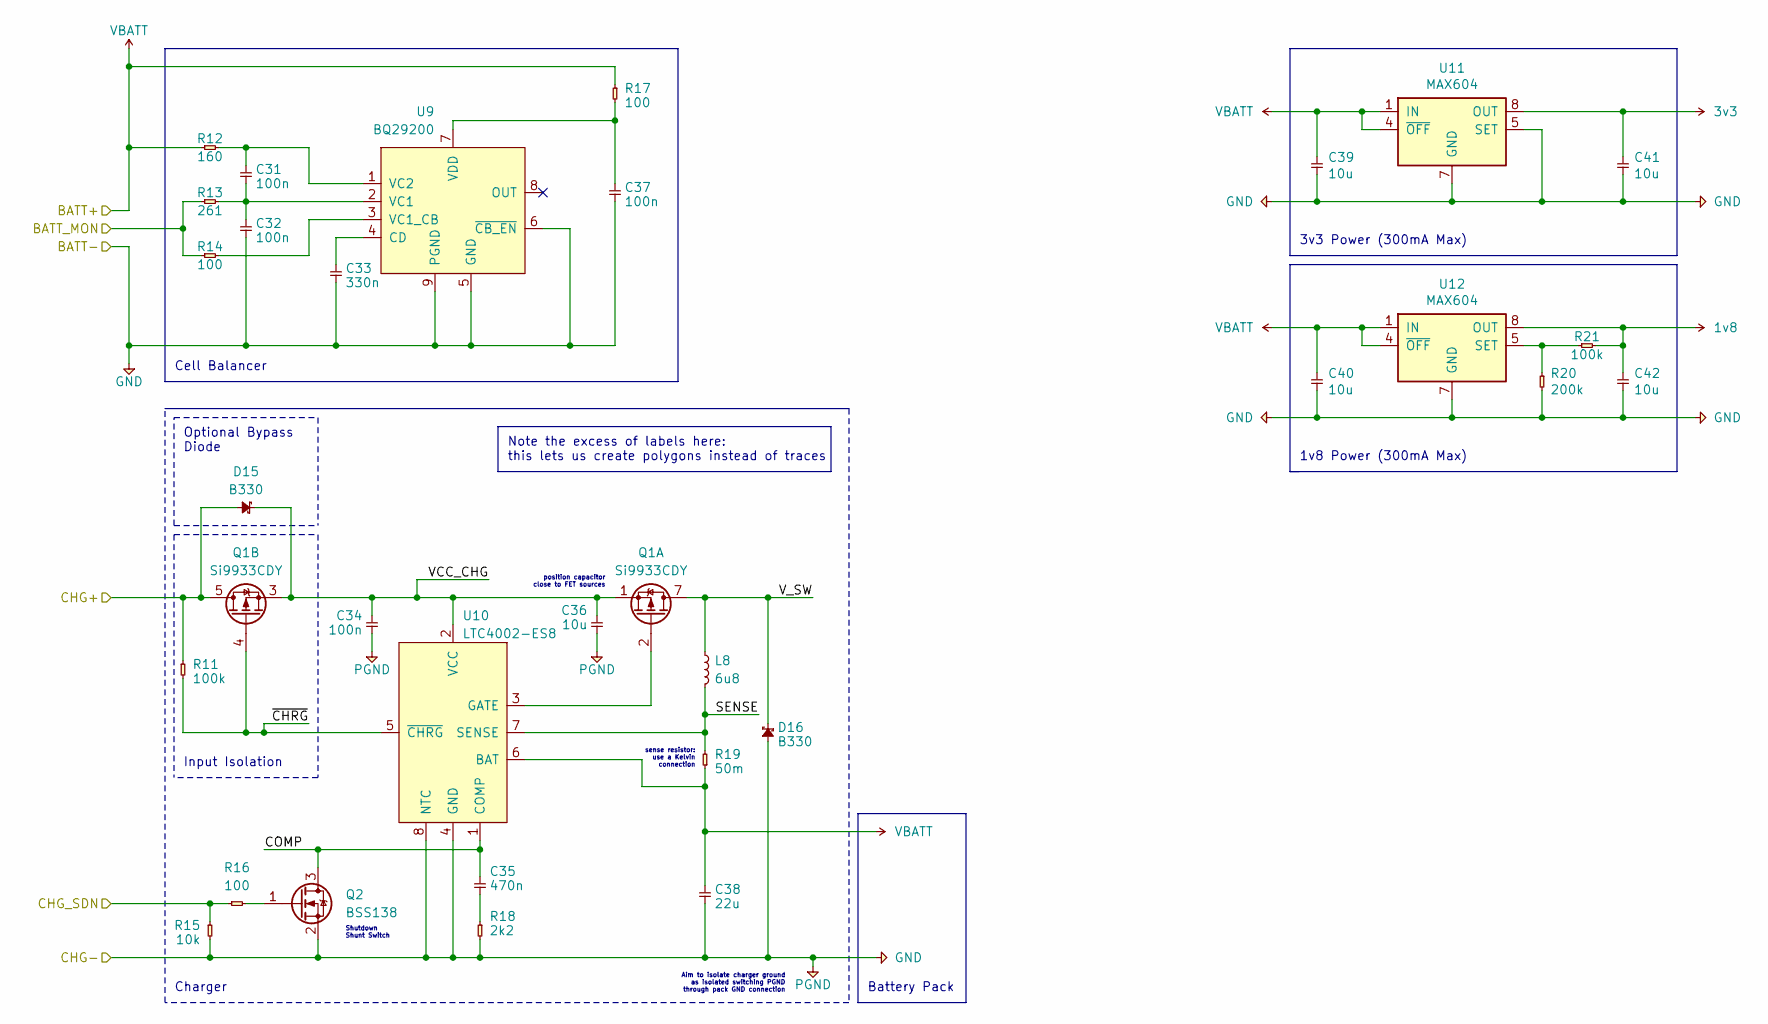
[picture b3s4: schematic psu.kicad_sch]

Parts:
C31, C32, C34, C37: 100n; C_0402; Farnell 1759166
C33: 330n; C_0402; Farnell 2346946
C35: 470n; C_0402; Farnell 2320847
C36: 10u; C_0402; Farnell 2611940
C38: 22u; C_0402; Farnell 2525135
C39, C40, C41, C42: 10u; C_0402
D15, D16: B330
L8: 6u8; L_Wuerth_HCI-7050
Q1: Si9933CDY; Farnell 1779275
Q2: BSS138
R11: 100k; R_0402; Farnell 2380290
R12: 160; R_0402; Farnell 2694996
R13: 261; R_0402; Farnell 2303485
R14, R17: 100; R_0402; Farnell 2447552
R15: 10k; R_0402; Farnell 1576464
R16: 100; R_0402; Farnell 2694996
R18: 2k2; R_0402; Farnell 1576464
R19: 50m; R_0402; Farnell 2008296
R20: 200k; R_0402
R21: 100k; R_0402
U9: BQ29200; Farnell 2383074
U10: LTC4002-ES8
U11, U12: MAX604

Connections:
1v8: C42.1, R21.2, U12.8 (OUT); also elsewhere on the board
3v3: C41.1, U11.8 (OUT); also elsewhere on the board
/CHG_SDN: R15.1, R16.1; also elsewhere on the board
/PSU/BATT_MON: R13.1, R14.1; also elsewhere on the board
/PSU/CHG+: D15.2, Q1.5 (D2), Q1.6 (D2), R11.1; also elsewhere on the board
/PSU/COMP: C35.1, Q2.3 (D), U10.1 (COMP)
/PSU/SENSE: L8.2, R19.2, U10.7 (SENSE)
/PSU/VCC_CHG: C34.1, C36.1, D15.1, Q1.1 (S1), Q1.3 (S2), U10.2 (VCC)
/PSU/V_SW: D16.1, L8.1, Q1.7 (D1), Q1.8 (D1)
/PSU/~CHRG: Q1.4 (G2), R11.2, U10.5 (~CHRG)
GND: C32.2, C33.2, C34.2, C36.2, C37.2, C38.2, C39.2, C40.2, C41.2, C42.2, D16.2, Q2.2 (S), R15.2, R18.2, R20.2, U9.5 (GND), U9.6 (~CB_EN), U9.9 (PGND), U10.4 (GND), U10.8 (NTC), U11.2 (GND), U11.3 (GND), U11.5 (SET), U11.6 (GND), U11.7 (GND), U12.2 (GND), U12.3 (GND), U12.6 (GND), U12.7 (GND); also elsewhere on the board
unnamed: C31.1, R12.2, U9.1 (VC2)
unnamed: C31.2, C32.1, R13.2, U9.2 (VC1)
unnamed: C33.1, U9.4 (CD)
unnamed: C35.2, R18.1
unnamed: C37.1, R17.2, U9.7 (VDD)
unnamed: Q1.2 (G1), U10.3 (GATE)
unnamed: Q2.1 (G), R16.2
unnamed: R14.2, U9.3 (VC1_CB)
unnamed: R20.1, R21.1, U12.5 (SET)
VBATT: C38.1, C39.1, C40.1, R12.1, R17.1, R19.1, U10.6 (BAT), U11.1 (IN), U11.4 (~OFF), U12.1 (IN), U12.4 (~OFF); also elsewhere on the board

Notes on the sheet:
Input Isolation
Battery Pack
Charger
sense resistor: use a Kelvin connection
Aim to isolate charger ground as isolated switching PGND through pack GND connection
Note the excess of labels here: this lets us create polygons instead of traces
Cell Balancer
Optional Bypass Diode
3v3 Power (300mA Max)
position capacitor close to FET sources
1v8 Power (300mA Max)
Shutdown Shunt Switch

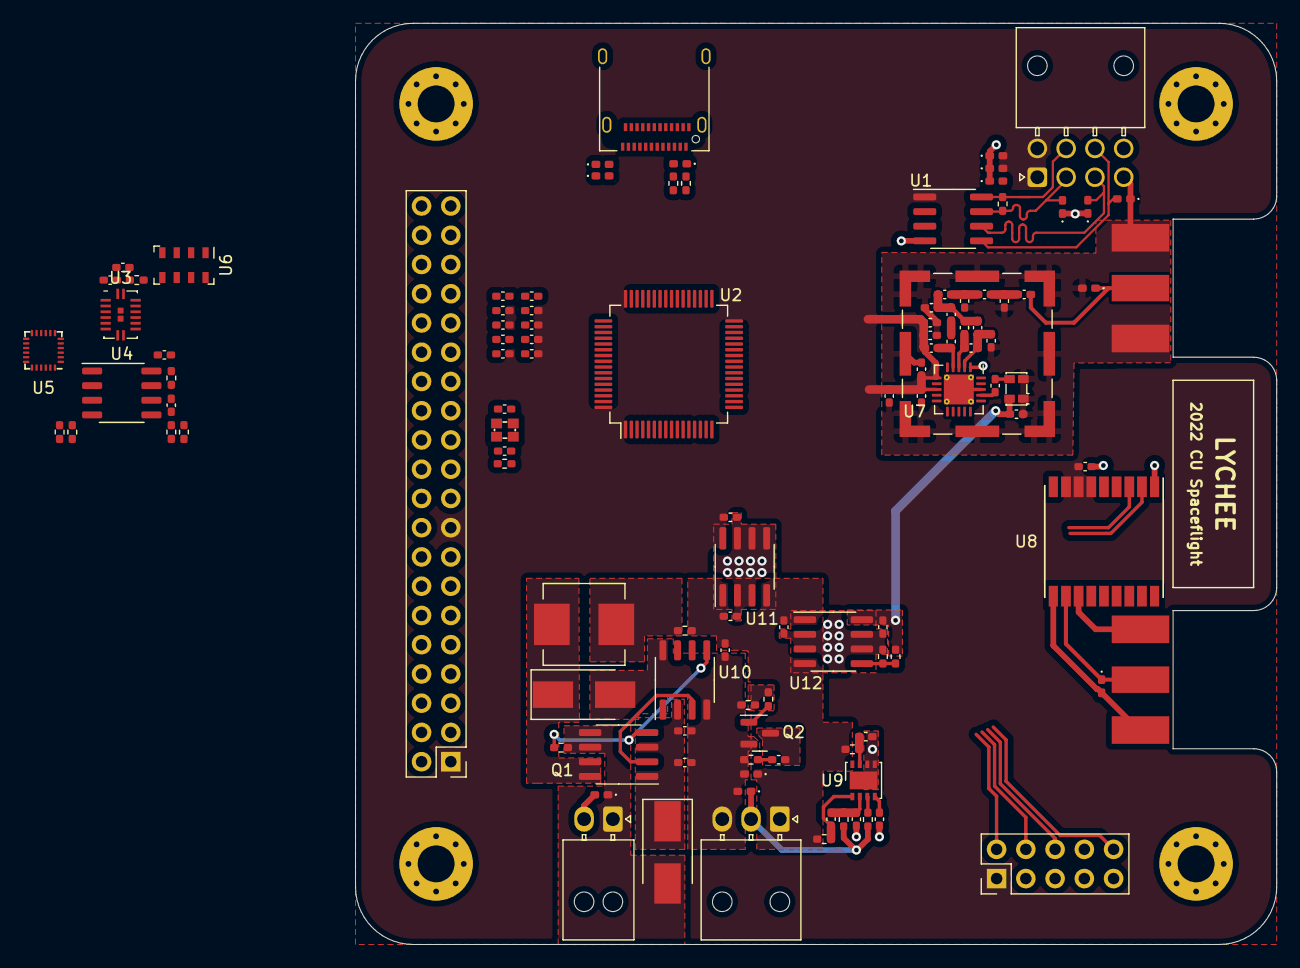
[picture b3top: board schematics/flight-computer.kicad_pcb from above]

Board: 4 copper layers, 80.0 x 80.0 mm, 116 parts (0 on the bottom side), 75 nets.
